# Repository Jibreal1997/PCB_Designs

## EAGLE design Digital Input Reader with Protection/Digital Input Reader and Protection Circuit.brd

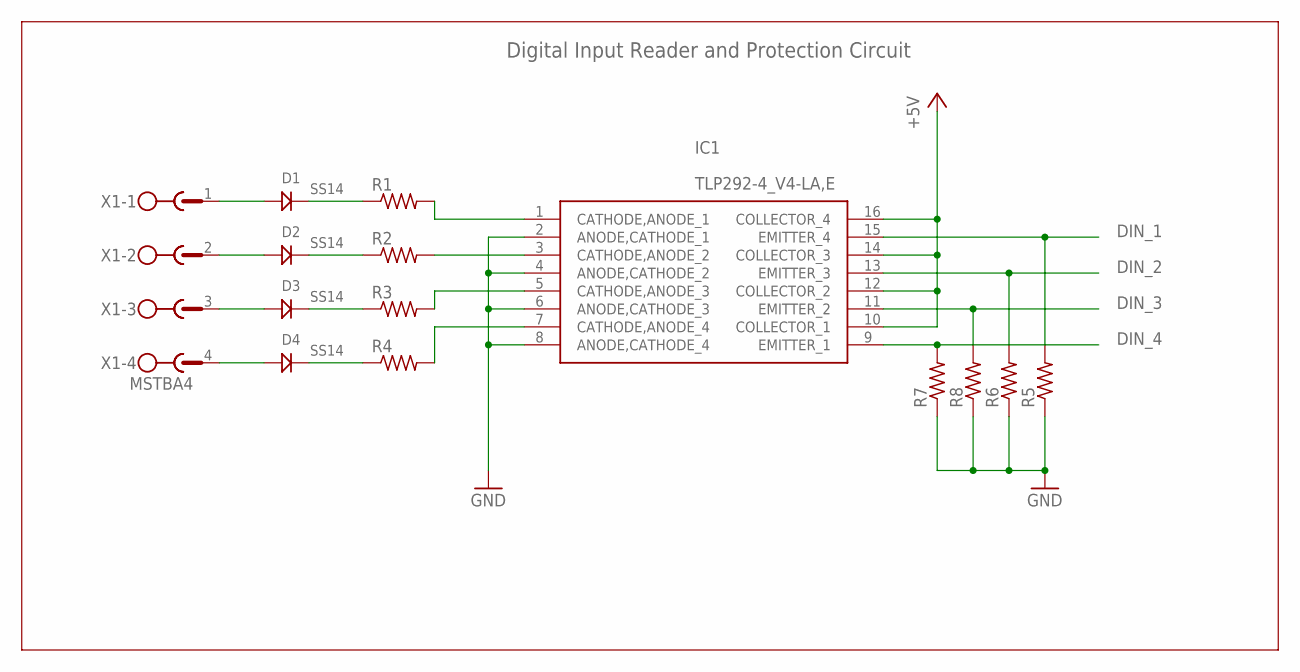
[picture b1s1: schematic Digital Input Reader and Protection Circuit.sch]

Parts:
D1, D2, D3, D4: SS14; DO214
IC1: TLP292-4_V4-LA,E; SOIC127P700X230-16N
R1, R2, R3, R4, R5, R6, R7, R8: R-US_R0805; R0805
X1: MSTBA4

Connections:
+5V: IC1.10 (COLLECTOR_1), IC1.12 (COLLECTOR_2), IC1.14 (COLLECTOR_3), IC1.16 (COLLECTOR_4)
DIN_1: IC1.15 (EMITTER_4), R5.2
DIN_2: IC1.13 (EMITTER_3), R6.2
DIN_3: IC1.11 (EMITTER_2), R8.2
DIN_4: IC1.9 (EMITTER_1), R7.2
GND: IC1.2 (ANODE,CATHODE_1), IC1.4 (ANODE,CATHODE_2), IC1.6 (ANODE,CATHODE_3), IC1.8 (ANODE,CATHODE_4), R5.1, R6.1, R7.1, R8.1
unnamed: D1.ANODE, X1.1
unnamed: D1.CATHODE (KATHODE), R1.1
unnamed: D2.ANODE, X1.2
unnamed: D2.CATHODE (KATHODE), R2.1
unnamed: D3.ANODE, X1.3
unnamed: D3.CATHODE (KATHODE), R3.1
unnamed: D4.ANODE, X1.4
unnamed: D4.CATHODE (KATHODE), R4.1
unnamed: IC1.1 (CATHODE,ANODE_1), R1.2
unnamed: IC1.3 (CATHODE,ANODE_2), R2.2
unnamed: IC1.5 (CATHODE,ANODE_3), R3.2
unnamed: IC1.7 (CATHODE,ANODE_4), R4.2

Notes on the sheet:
Digital Input Reader and Protection Circuit

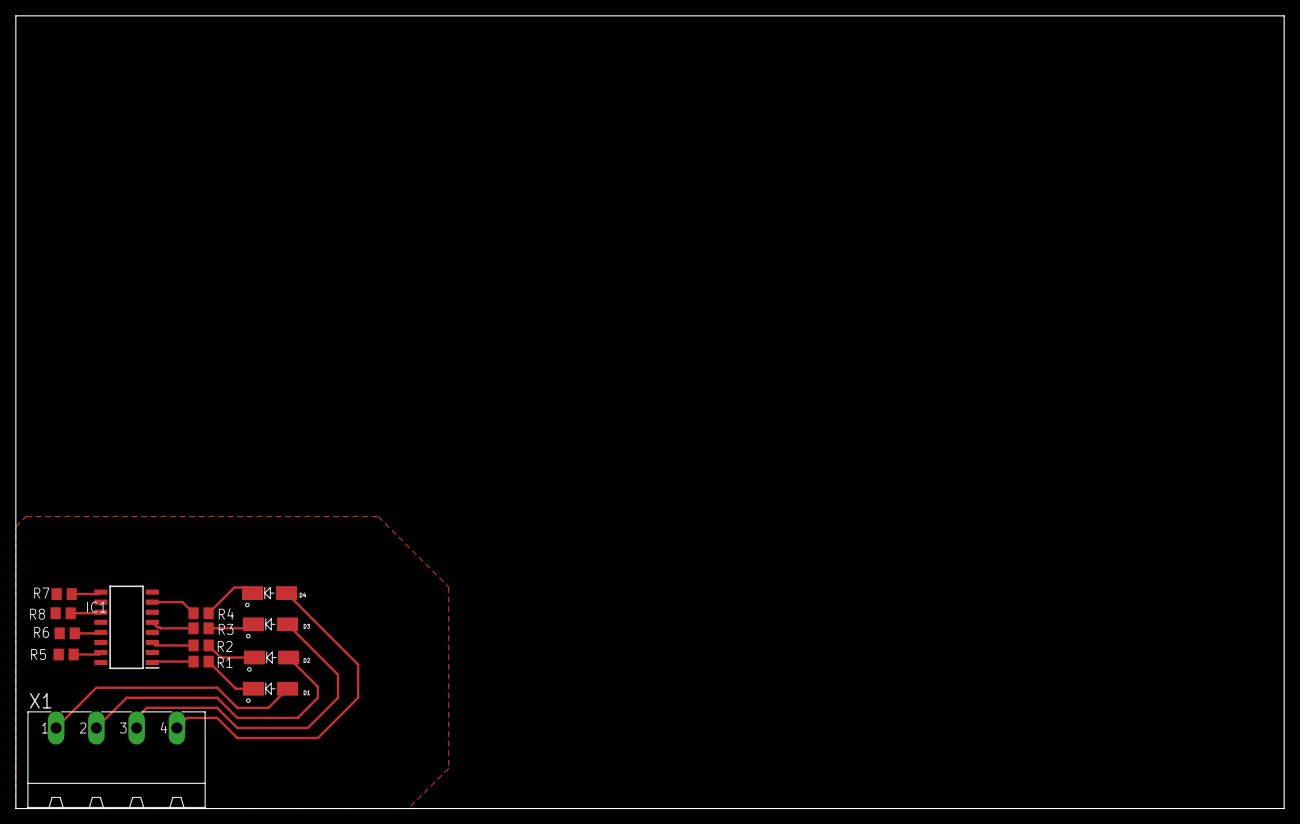
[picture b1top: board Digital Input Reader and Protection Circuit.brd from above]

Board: 2 copper layers, 160.0 x 100.0 mm, 14 parts (0 on the bottom side), 18 nets.

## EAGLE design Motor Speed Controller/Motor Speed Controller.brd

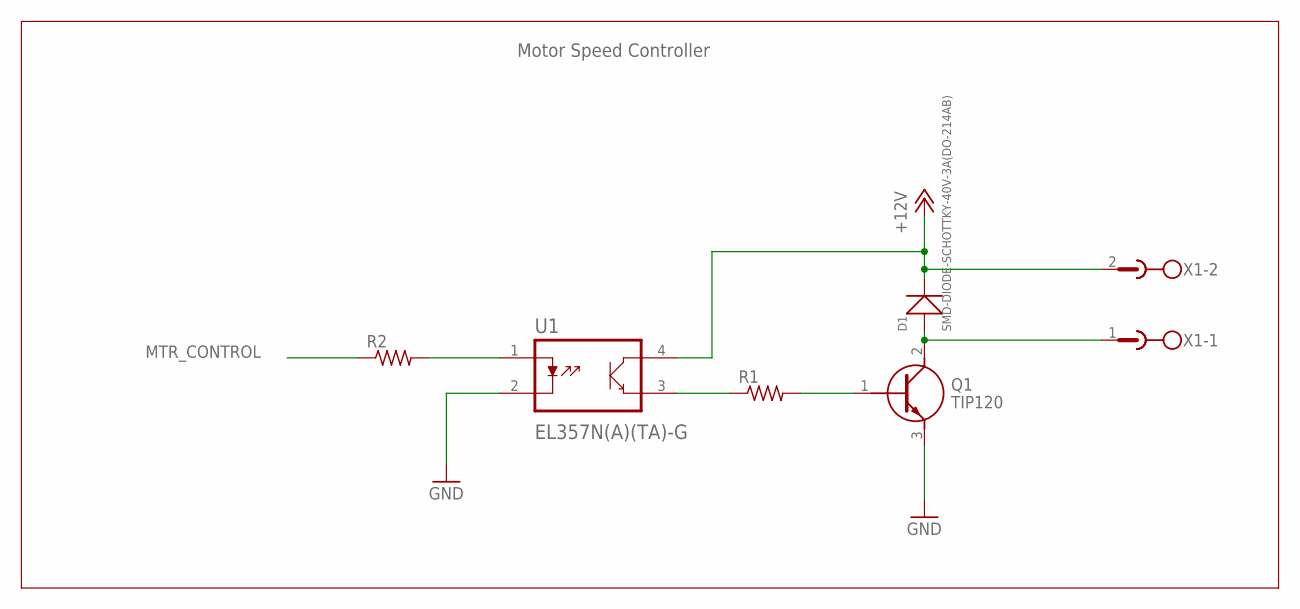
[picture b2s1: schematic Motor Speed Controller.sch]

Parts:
D1: SMD-DIODE-SCHOTTKY-40V-3A(DO-214AB); DO-214AB
Q1: TIP120; TO220
R1, R2: R-US_R0805; R0805
U1: EL357N(A)(TA)-G; SOP254P700X200-4N
X1: MSTBA4

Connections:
+12V: D1.2 (-), U1.4 (C), X1.2
GND: Q1.3 (E), U1.2 (K)
MTR_CONTROL: R2.1
unnamed: R2.2, U1.1 (A)
unnamed: R1.1, U1.3 (E)
unnamed: Q1.1 (B), R1.2
unnamed: D1.1 (+), Q1.2 (C), X1.1

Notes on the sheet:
Motor Speed Controller

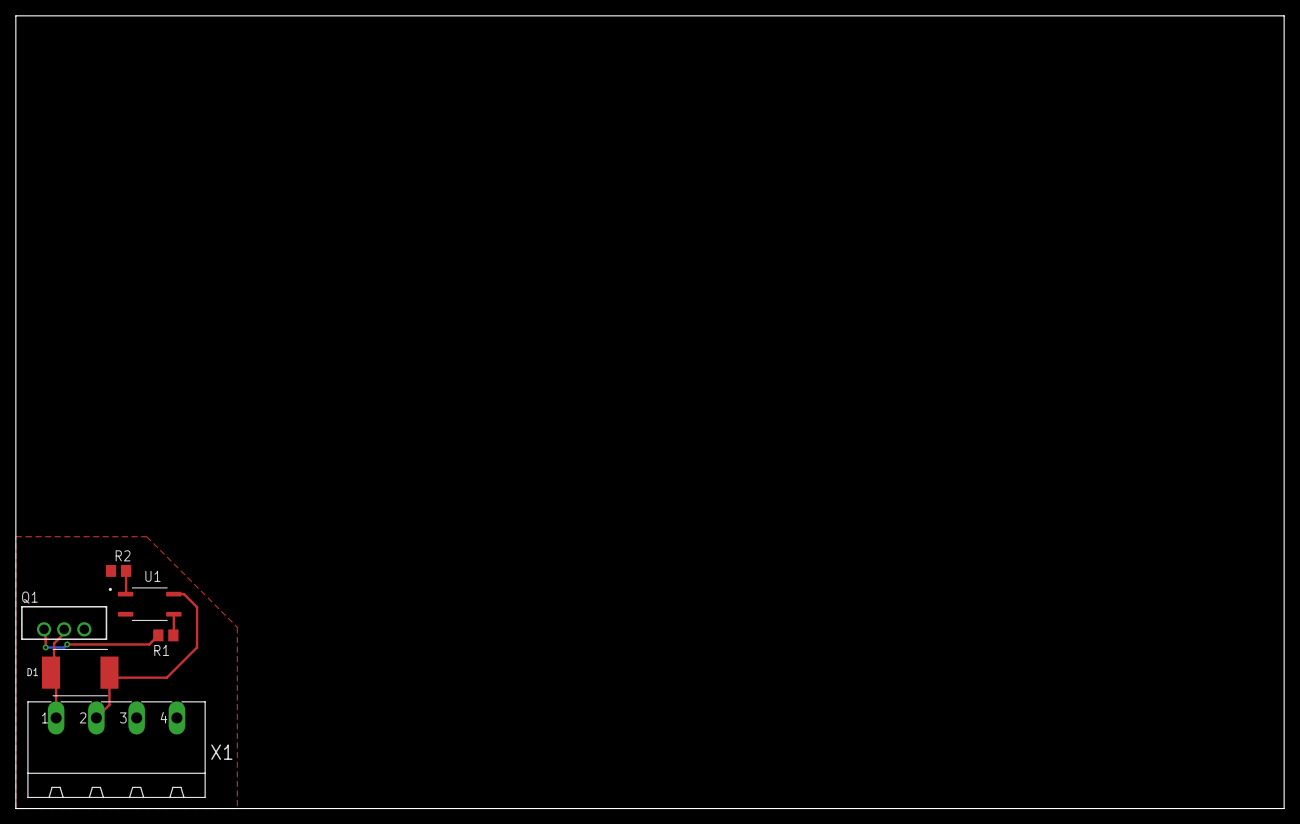
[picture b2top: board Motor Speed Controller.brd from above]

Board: 2 copper layers, 160.0 x 100.0 mm, 6 parts (0 on the bottom side), 6 nets.

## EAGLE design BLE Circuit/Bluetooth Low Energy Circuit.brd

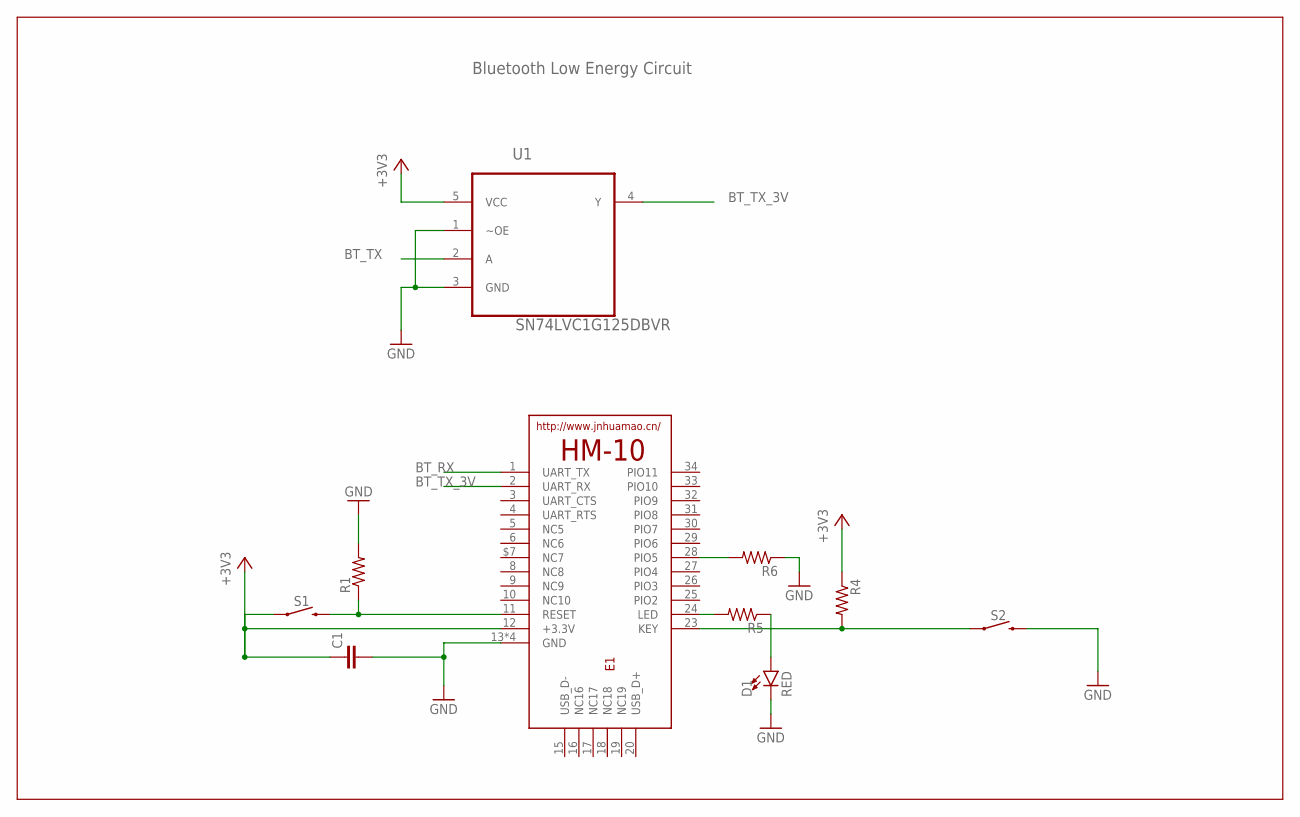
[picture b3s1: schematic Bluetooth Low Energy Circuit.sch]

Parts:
C1: C-EUC0805; C0805
D1: RED; LED-0603
E1: HM-10-BOARD; 26.9X13X2.2_BOARD
R1, R4, R5, R6: R-US_R0805; R0805
S1, S2: MOMENTARY-SWITCH-SPST-SMD-6.0X3.5MM; TACTILE_SWITCH_SMD_6.0X3.5MM
U1: SN74LVC1G125DBVR; SOT95P280X145-5N

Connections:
+3V3: C1.1, E1.12 (+3.3V), R4.1, S1.1, U1.5 (VCC)
BT_RX: E1.1 (UART_TX)
BT_TX: U1.2 (A)
BT_TX_3V: E1.2 (UART_RX), U1.4 (Y)
GND: C1.2, D1.C, E1.13 (GND), E1.14 (GND), E1.21 (GND), E1.22 (GND), R1.2, R6.1, S2.2, U1.1 (~OE), U1.3 (GND)
unnamed: E1.11 (RESET), R1.1, S1.2
unnamed: E1.23 (KEY), R4.2, S2.1
unnamed: E1.24 (LED), R5.2
unnamed: E1.28 (PIO5), R6.2
unnamed: D1.A, R5.1

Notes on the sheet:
Bluetooth Low Energy Circuit

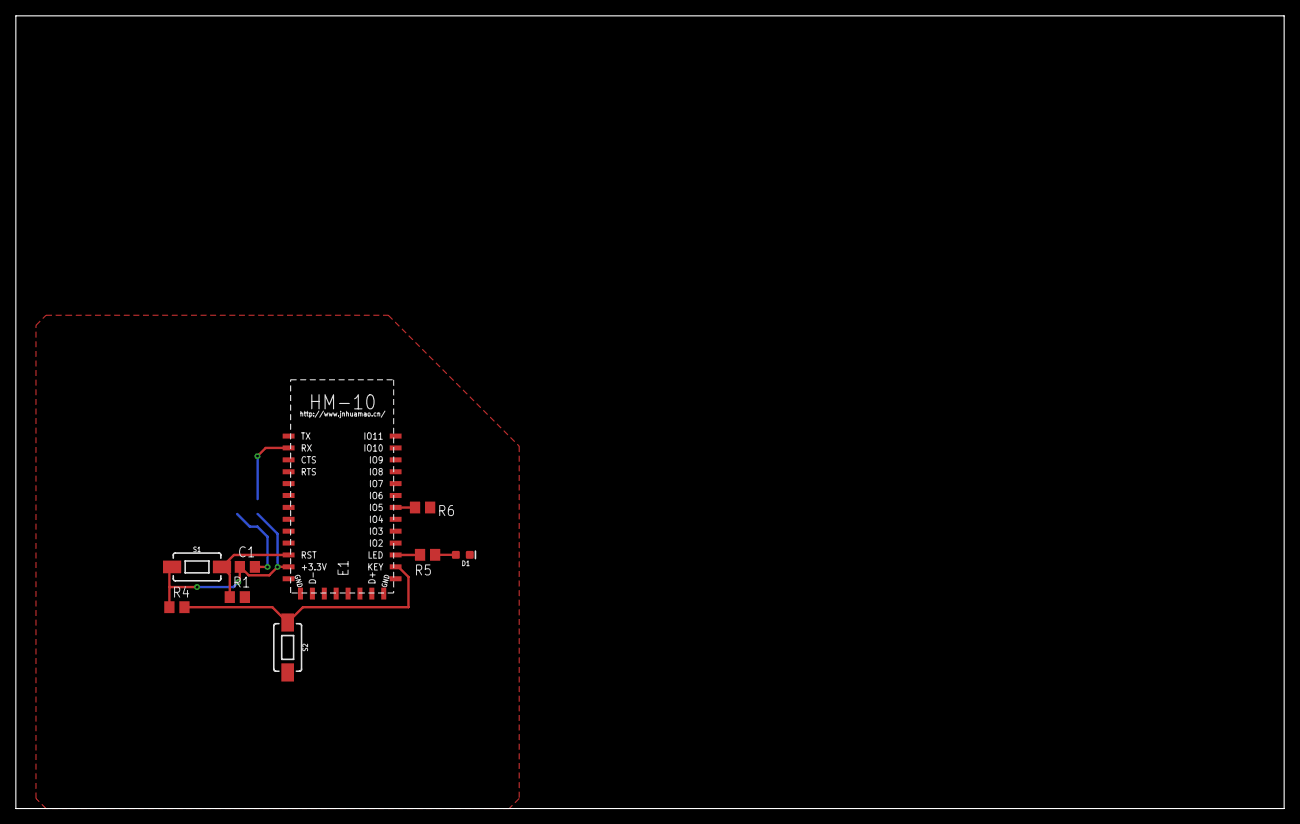
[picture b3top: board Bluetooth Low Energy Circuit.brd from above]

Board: 2 copper layers, 160.0 x 100.0 mm, 10 parts (1 on the bottom side), 8 nets.

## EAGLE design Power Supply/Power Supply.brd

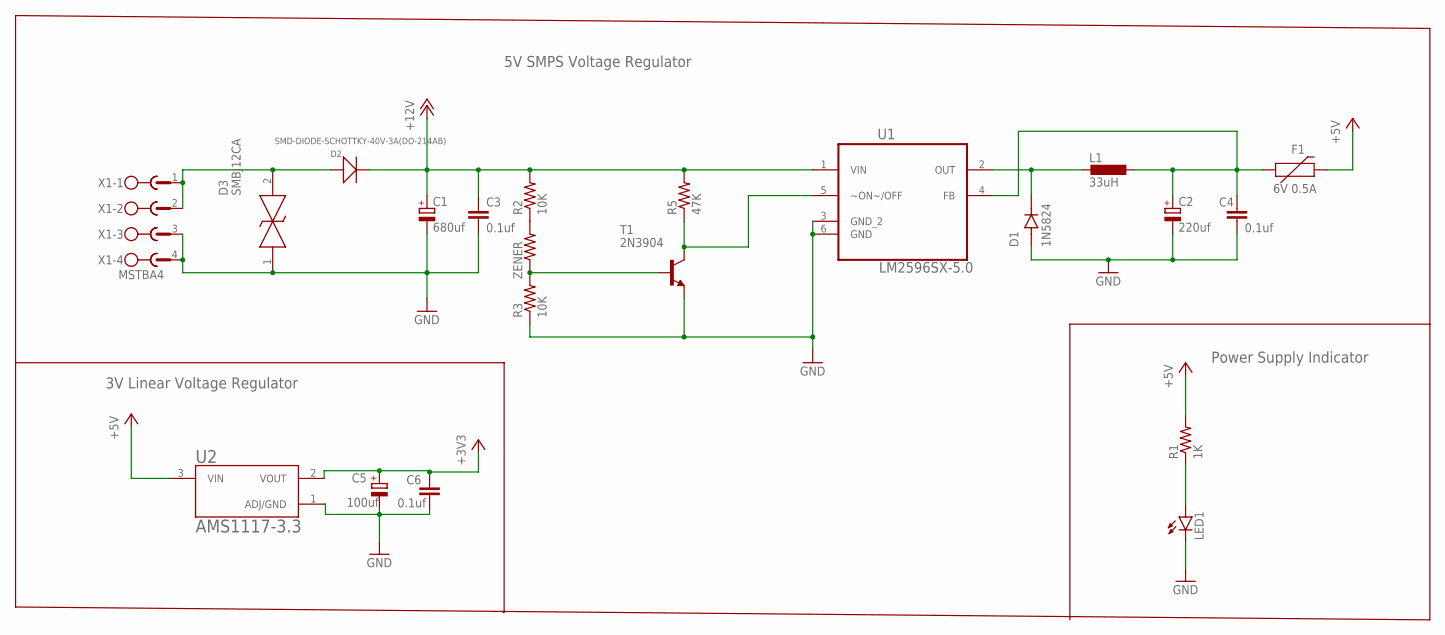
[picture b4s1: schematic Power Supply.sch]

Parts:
C1: 680uf; SMC_B
C2: 220uf; SMC_B
C3, C4, C6: 0.1uf; C0805
C5: 100uf; SMC_B
D1: 1N5824; DIOAD1898W129L762D1143
D2: SMD-DIODE-SCHOTTKY-40V-3A(DO-214AB); DO-214AB
D3: SMBJ12CA; DIONM5443X244N
F1: 6V 0.5A; 0805
L1: 33uH; L1812
LED1: LED3MM
R1: 1K; R0805
R2, R3: 10K; R0805
R5: 47K; 0204/7
T1: 2N3904; TO92
U1: LM2596SX-5.0; TO170P1435X465-6N
U2: AMS1117-3.3; SOT229P700X180-4N
X1: MSTBA4
ZENER: R-US_0204/7; 0204/7

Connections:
+3V3: C5.+, C6.1, U2.2 (VOUT)
+5V: F1.2, R1.2, U2.3 (VIN)
+12V: C1.+, C3.1, D2.2 (-), R2.2, R5.2, U1.1 (VIN)
GND: C1.-, C2.-, C3.2, C4.2, C5.-, C6.2, D1.A, D3.1, LED1.K (C), R3.1, T1.3 (E), U1.3 (GND_2), U1.6 (GND), U2.1 (ADJ/GND), X1.3, X1.4
unnamed: D1.C (K), L1.2, U1.2 (OUT)
unnamed: LED1.A, R1.1
unnamed: D2.1 (+), D3.2, X1.1, X1.2
unnamed: R2.1, ZENER.2
unnamed: R3.2, T1.2 (B), ZENER.1
unnamed: R5.1, T1.1 (C), U1.5 (~ON~/OFF)
unnamed: C2.+, C4.1, F1.1, L1.1, U1.4 (FB)

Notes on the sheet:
5V SMPS Voltage Regulator
3V Linear Voltage Regulator
Power Supply Indicator

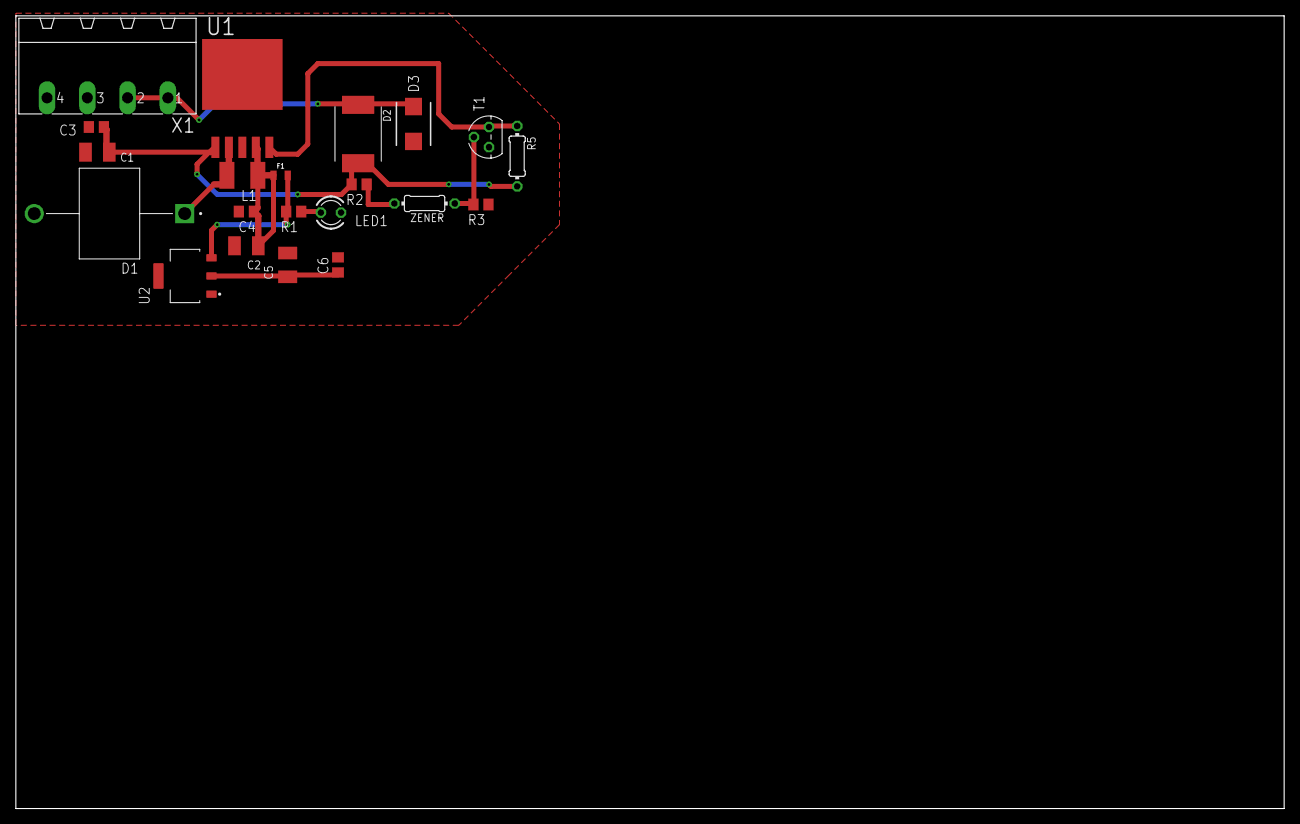
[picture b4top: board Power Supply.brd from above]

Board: 2 copper layers, 160.0 x 100.0 mm, 21 parts (0 on the bottom side), 11 nets.

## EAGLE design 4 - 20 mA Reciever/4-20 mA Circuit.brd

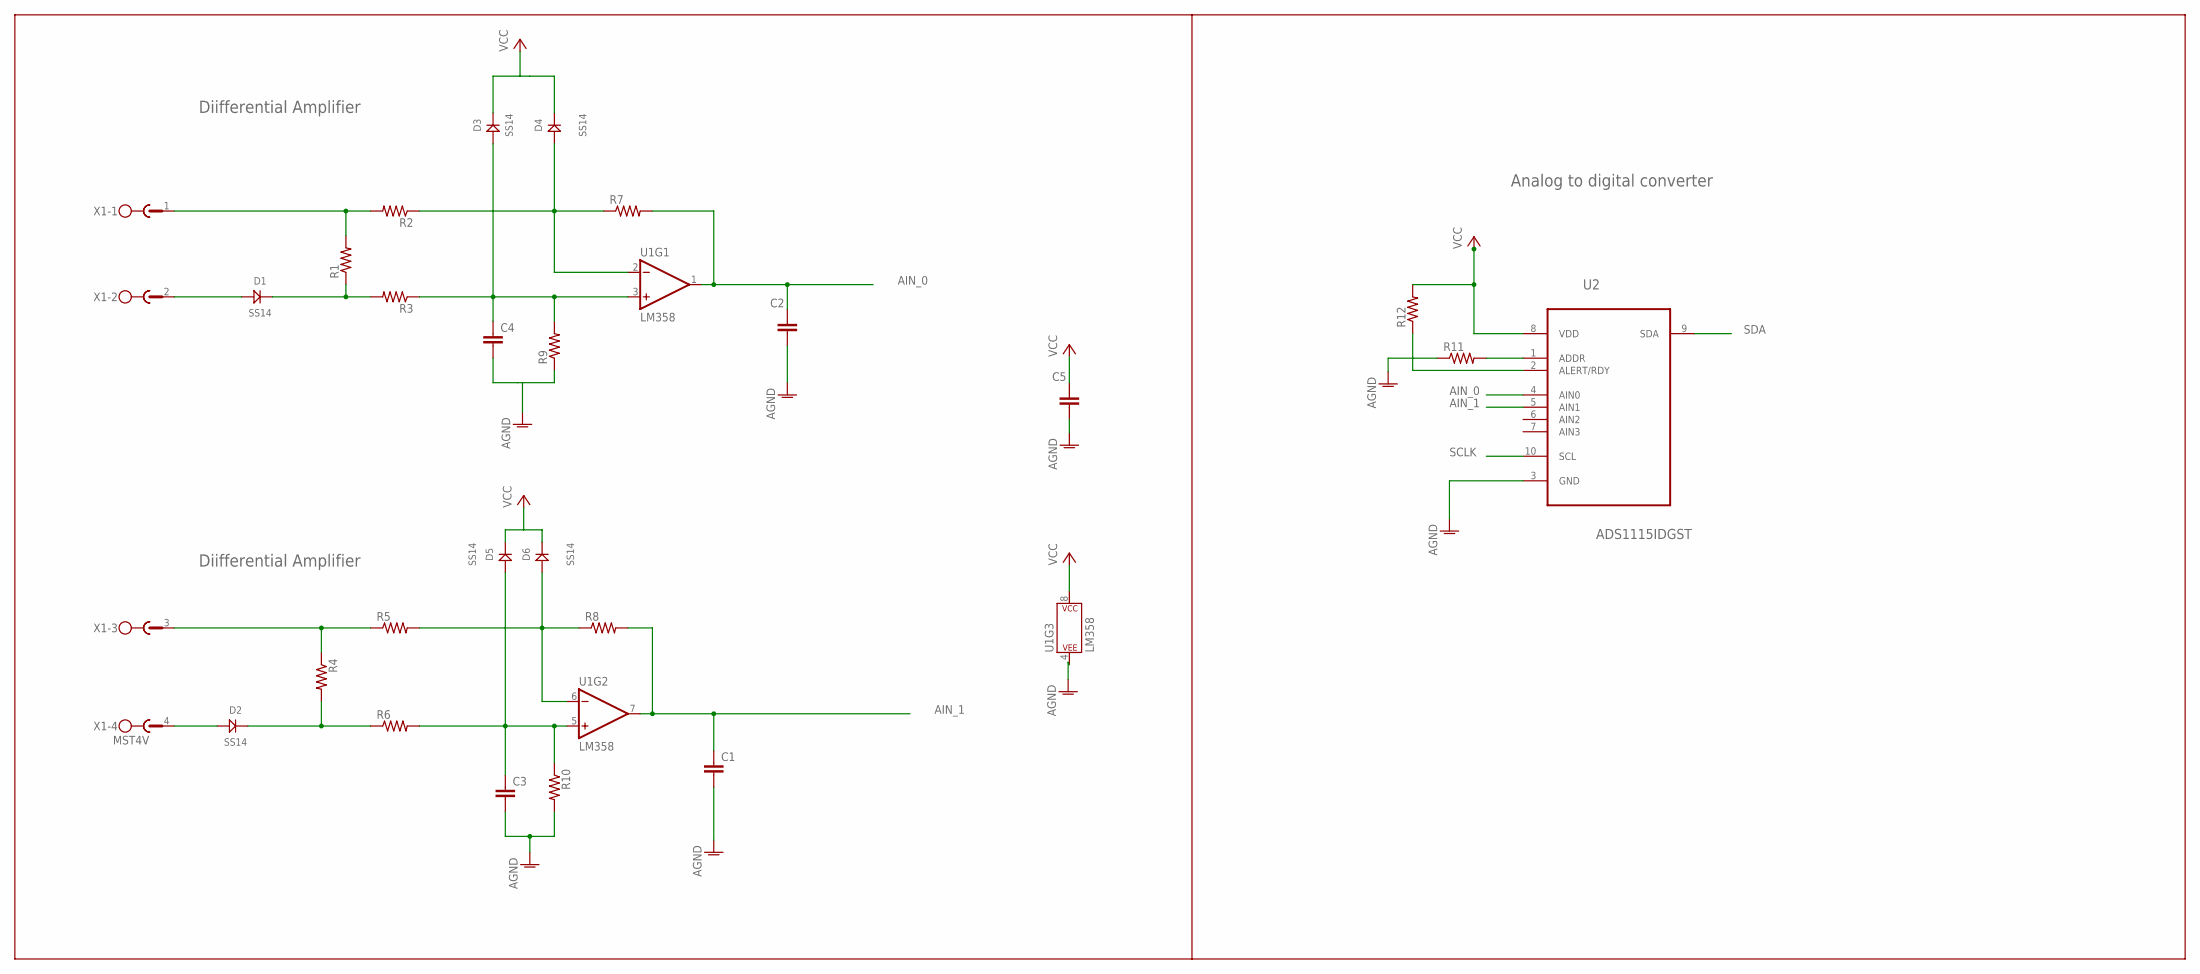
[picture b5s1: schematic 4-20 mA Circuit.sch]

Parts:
C1, C2, C3, C4, C5: C-EUC0805; C0805
D1, D2, D3, D4, D5, D6: SS14; DO214
R1, R2, R3, R4, R5, R6, R7, R8, R9, R10, R11, R12: R-US_R0805; R0805
U1: LM358; DIP08
U2: ADS1115IDGST; SOP50P490X110-10N
X1: MST4V; MSTBV4

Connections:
AGND: C1.2, C2.2, C3.2, C4.2, C5.2, R9.1, R10.2, R11.1, U1.4 (P$V-), U2.3 (GND)
AIN_0: C2.1, R7.2, U1.1 (OUT), U2.4 (AIN0)
AIN_1: C1.1, R8.2, U1.7 (OUT), U2.5 (AIN1)
unnamed: R1.2, R2.2, X1.1
unnamed: D1.CATHODE (KATHODE), R1.1, R3.2
unnamed: C4.1, D3.ANODE, R3.1, R9.2, U1.3 (+IN)
unnamed: D1.ANODE, X1.2
unnamed: R4.1, R5.1, X1.3
unnamed: D4.ANODE, R2.1, R7.1, U1.2 (-IN)
unnamed: D2.CATHODE (KATHODE), R4.2, R6.1
unnamed: D6.ANODE, R5.2, R8.1, U1.6 (-IN)
unnamed: C3.1, D5.ANODE, R6.2, R10.1, U1.5 (+IN)
unnamed: D2.ANODE, X1.4
unnamed: R12.1, U2.2 (ALERT/RDY)
unnamed: R11.2, U2.1 (ADDR)
SCLK: U2.10 (SCL)
SDA: U2.9 (SDA)
VCC: C5.1, D3.CATHODE (KATHODE), D4.CATHODE (KATHODE), D5.CATHODE (KATHODE), D6.CATHODE (KATHODE), R12.2, U1.8 (P$V+), U2.8 (VDD)

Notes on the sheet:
Diifferential Amplifier
Analog to digital converter

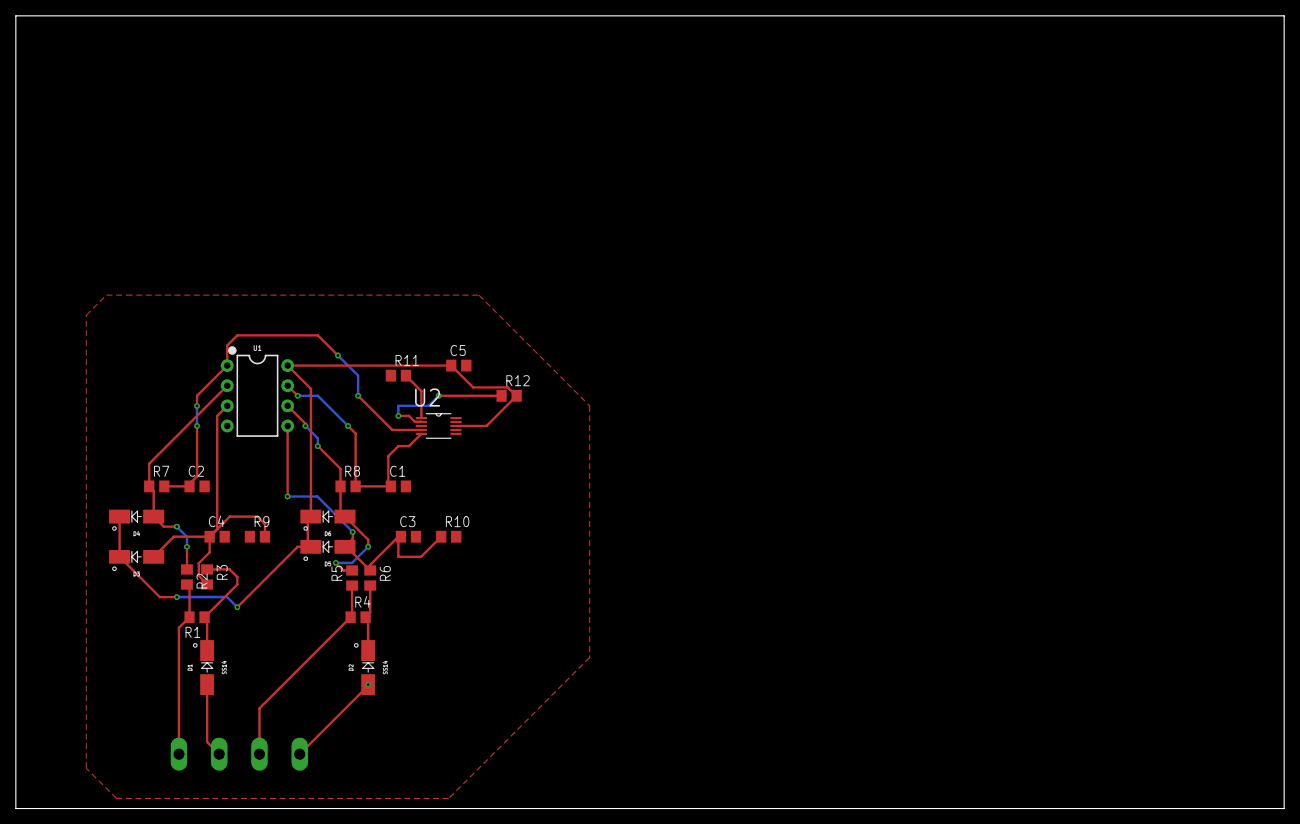
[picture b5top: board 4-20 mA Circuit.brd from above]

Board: 2 copper layers, 160.0 x 100.0 mm, 26 parts (1 on the bottom side), 16 nets.

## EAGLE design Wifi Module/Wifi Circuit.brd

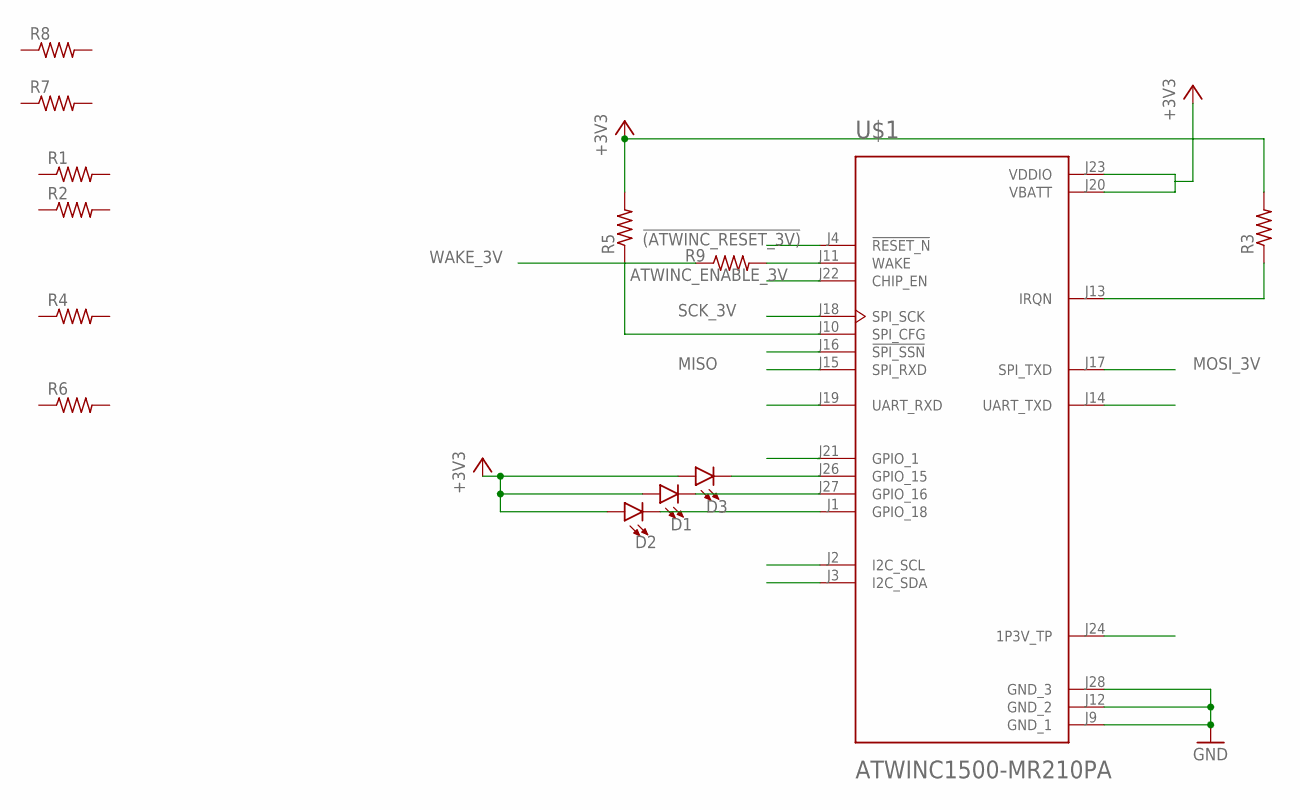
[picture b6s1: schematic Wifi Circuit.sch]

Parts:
D1, D2, D3: LED3MM; LED_3MM
R1, R2, R3, R4, R5, R6, R7, R8, R9: R-US_R0805; R0805
U$1: ATWINC1500-MR210PA; ATMEL_ATWINC1500-MR210PA

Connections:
!(ATWINC_RESET_3V): U$1.J4 (!RESET_N)
+3V3: D1.A, D2.A, D3.A, R1.2, R3.2, R5.2, U$1.J20 (VBATT), U$1.J23 (VDDIO)
ATWINC_ENABLE_3V: R1.1, U$1.J22 (CHIP_EN); also elsewhere on the board
D12: U$1.J3 (I2C_SDA)
GND: U$1.J9 (GND_1), U$1.J12 (GND_2), U$1.J28 (GND_3)
MISO: U$1.J15 (SPI_RXD)
MOSI_3V: U$1.J17 (SPI_TXD)
unnamed: R9.2, U$1.J11 (WAKE)
unnamed: R5.1, U$1.J10 (SPI_CFG)
unnamed: R3.1, U$1.J13 (IRQN)
unnamed: D3.K (C), U$1.J26 (GPIO_15)
unnamed: D1.K (C), U$1.J27 (GPIO_16)
unnamed: D2.K (C), U$1.J1 (GPIO_18)
SCK_3V: U$1.J18 (SPI_SCK)
WAKE_3V: R9.1

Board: 2 copper layers, 14 parts (0 on the bottom side), 9 nets, no tracks yet.

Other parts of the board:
R10: R0805

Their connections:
ATWINC_ENABLE_3V: R10.2; also elsewhere on the board

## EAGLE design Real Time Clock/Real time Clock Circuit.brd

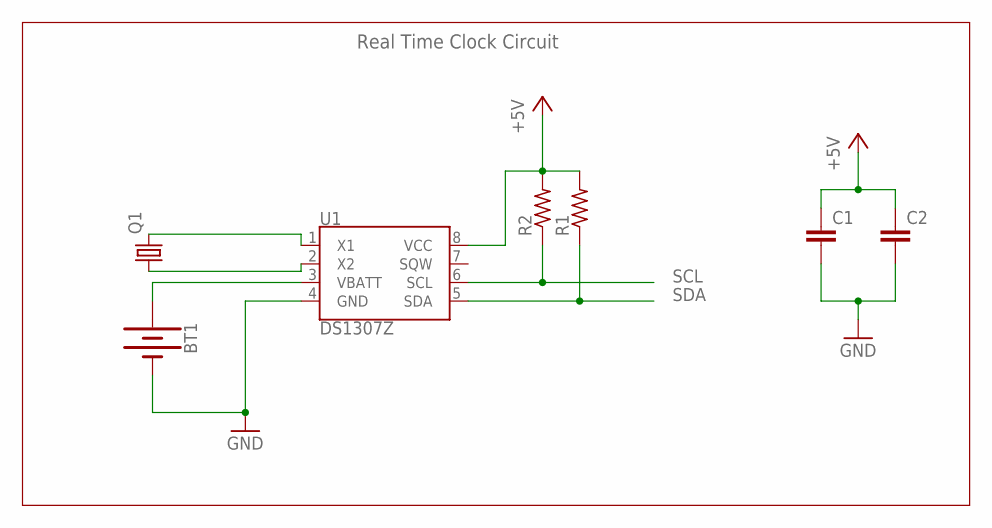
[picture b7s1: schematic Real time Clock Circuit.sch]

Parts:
BT1: BATTERY-20MM_PTH; BATTCOM_20MM_PTH
C1, C2: C-EUC0805; C0805
Q1: CRYSTALMM39SL; MM39SL
R1, R2: R-US_R0805; R0805
U1: DS1307Z; SO08-0.15

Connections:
+5V: C1.1, C2.1, R1.2, R2.2, U1.8 (VCC)
GND: BT1.2 (-), C1.2, C2.2, U1.4 (GND)
unnamed: Q1.4 (2), U1.1 (X1)
unnamed: Q1.1, U1.2 (X2)
unnamed: BT1.1 (+), U1.3 (VBATT)
SCL: R2.1, U1.6 (SCL)
SDA: R1.1, U1.5 (SDA)

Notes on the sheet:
Real Time Clock Circuit

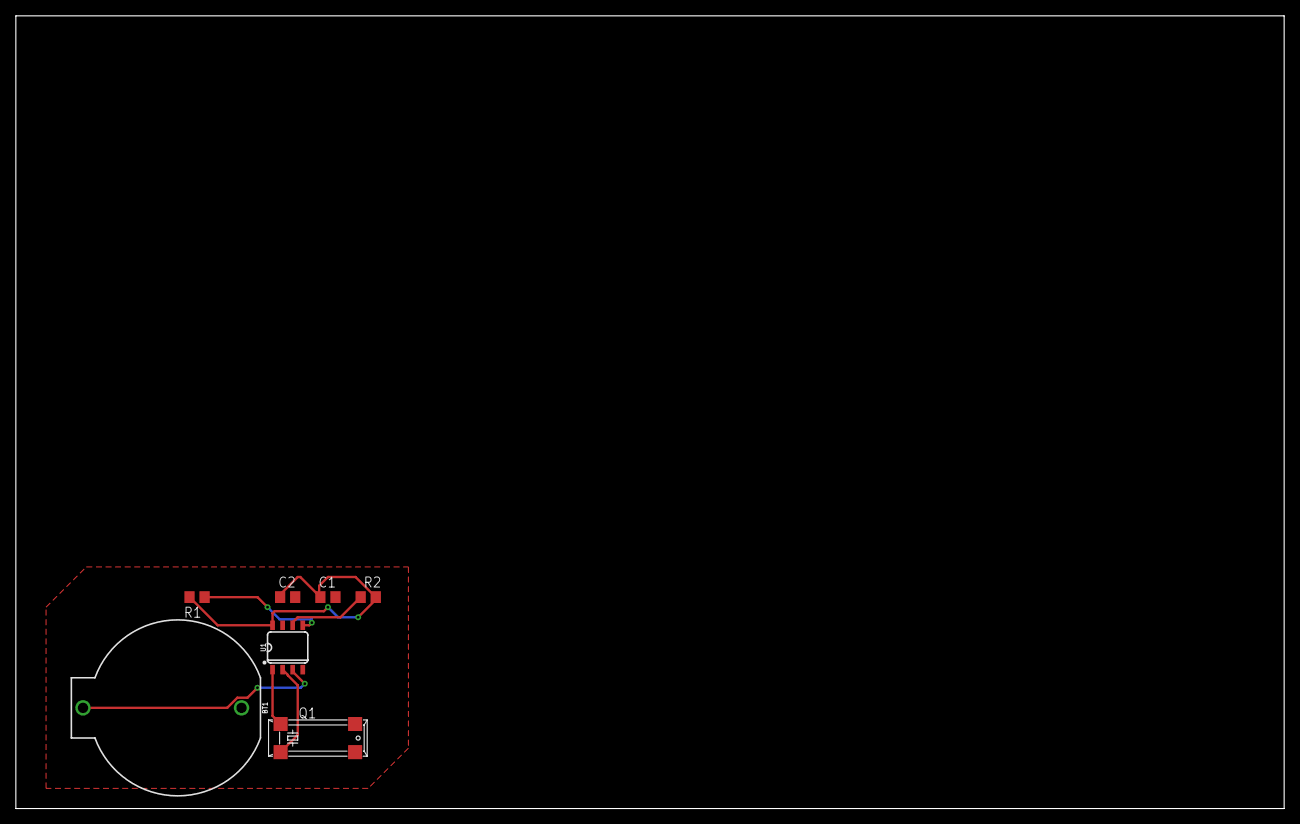
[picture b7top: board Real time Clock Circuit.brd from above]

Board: 2 copper layers, 160.0 x 100.0 mm, 7 parts (0 on the bottom side), 7 nets.

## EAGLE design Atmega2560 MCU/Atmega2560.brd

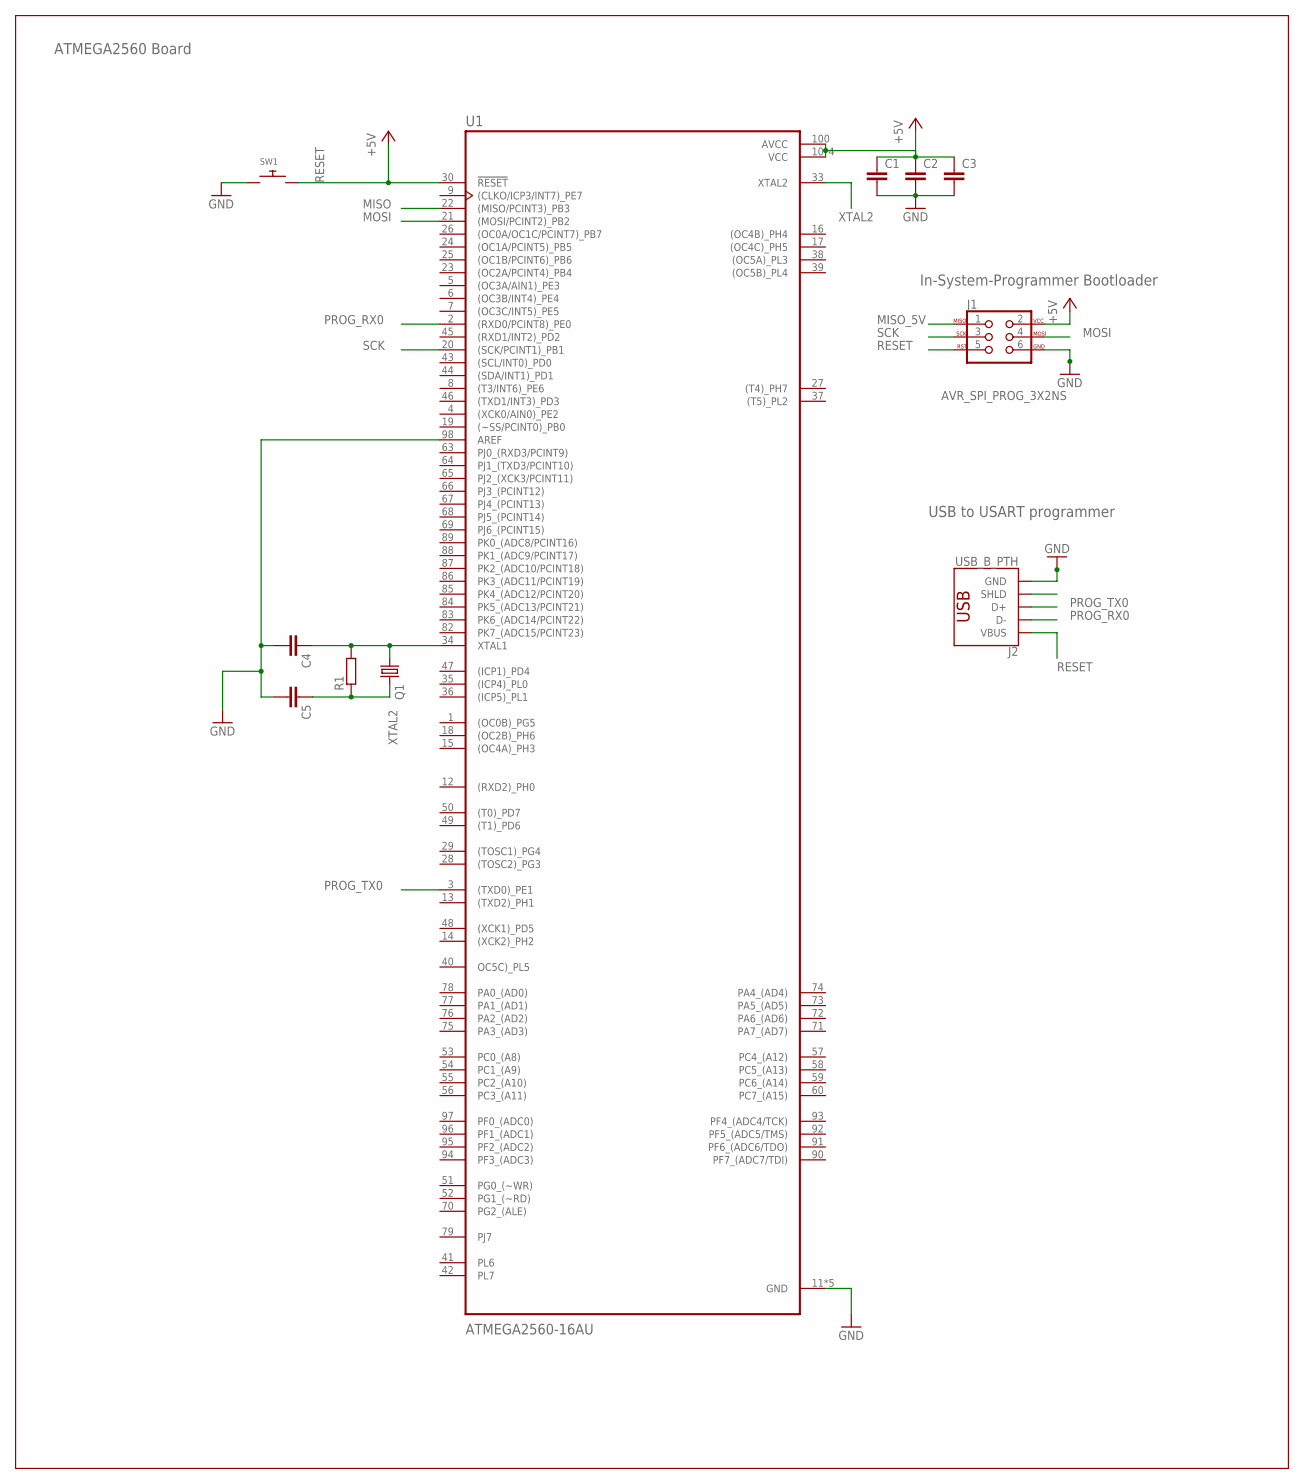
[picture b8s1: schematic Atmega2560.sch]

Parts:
C1, C2, C3, C4, C5: C-EUC0805; C0805
J1: AVR_SPI_PROG_3X2NS; 2X3-NS
J2: USB_B_PTH; USB-B-PTH
Q1: CRYSTALHC49S; HC49/S
R1: R-EU_0207/10; 0207/10
SW1: SWITCH_PUSHBUTTONEVQ-PE; TACT_PANA-EVQ
U1: ATMEGA2560-16AU; QFP50P1600X1600X120-100N

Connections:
+5V: C1.1, C2.1, C3.1, J1.2, U1.10 (VCC), U1.31 (VCC), U1.61 (VCC), U1.80 (VCC), U1.100 (AVCC)
GND: C1.2, C2.2, C3.2, C4.2, C5.2, J1.6, J2.GND, SW1.P$1, U1.11 (GND), U1.32 (GND), U1.62 (GND), U1.81 (GND), U1.98 (AREF), U1.99 (GND)
MISO: U1.22 ((MISO/PCINT3)_PB3)
MISO_5V: J1.1
MOSI: J1.4, U1.21 ((MOSI/PCINT2)_PB2)
unnamed: C4.1, Q1.1, R1.2, U1.34 (XTAL1)
unnamed: J2.SHLD1 (SHLD), J2.SHLD2 (SHLD)
PROG_RX0: J2.D-, U1.2 ((RXD0/PCINT8)_PE0)
PROG_TX0: J2.D+, U1.3 ((TXD0)_PE1)
RESET: J1.5, J2.VBUS, SW1.P$2, U1.30 (!RESET)
SCK: J1.3, U1.20 ((SCK/PCINT1)_PB1)
XTAL2: C5.1, Q1.2, R1.1, U1.33 (XTAL2)

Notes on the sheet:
ATMEGA2560 Board
In-System-Programmer Bootloader
USB to USART programmer

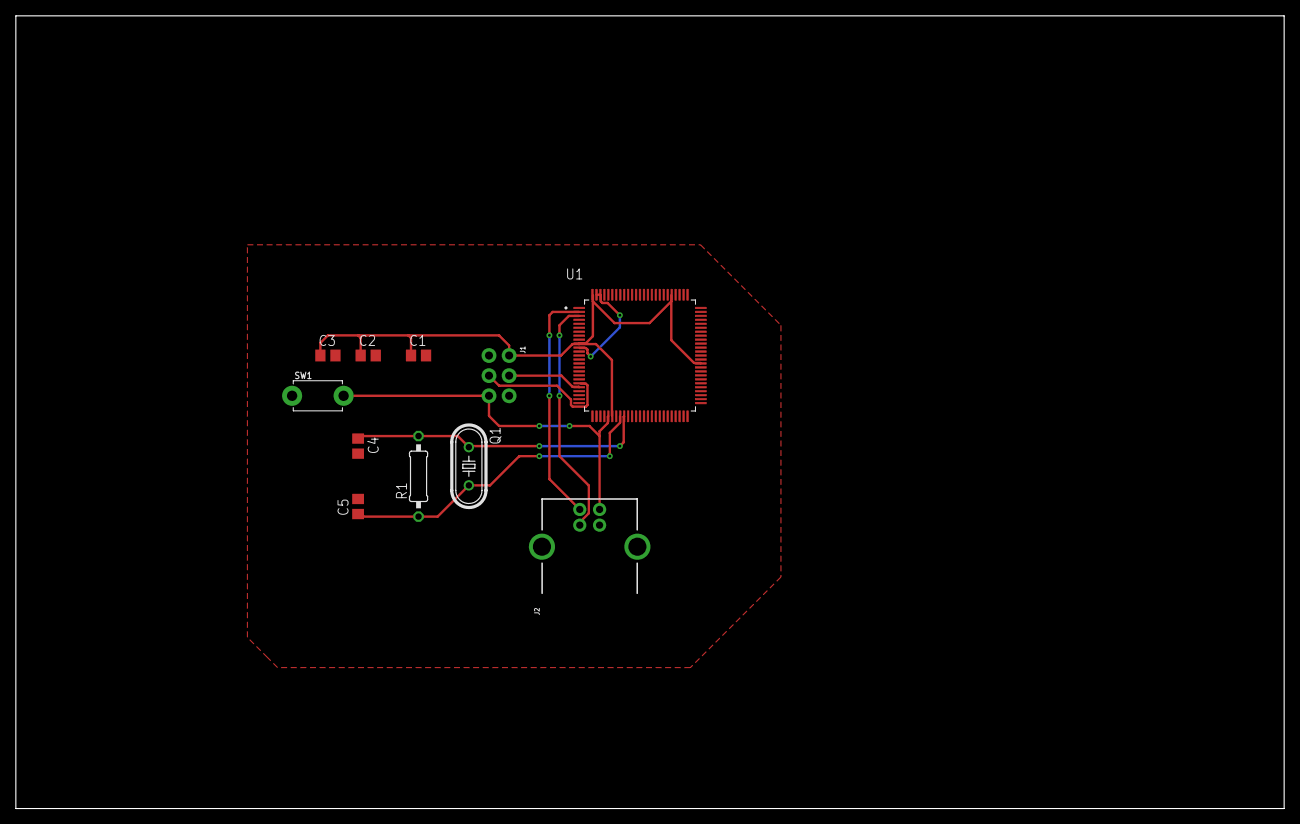
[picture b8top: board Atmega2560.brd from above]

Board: 2 copper layers, 160.0 x 100.0 mm, 11 parts (0 on the bottom side), 10 nets.

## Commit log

2022-01-03 Added all folders

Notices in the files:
parts and their libraries:
SparkFun-IC-Amplifiers: Licensing: Creative Commons ShareAlike 4.0 International - https://creativecommons.org/licenses/by-sa/4.0
